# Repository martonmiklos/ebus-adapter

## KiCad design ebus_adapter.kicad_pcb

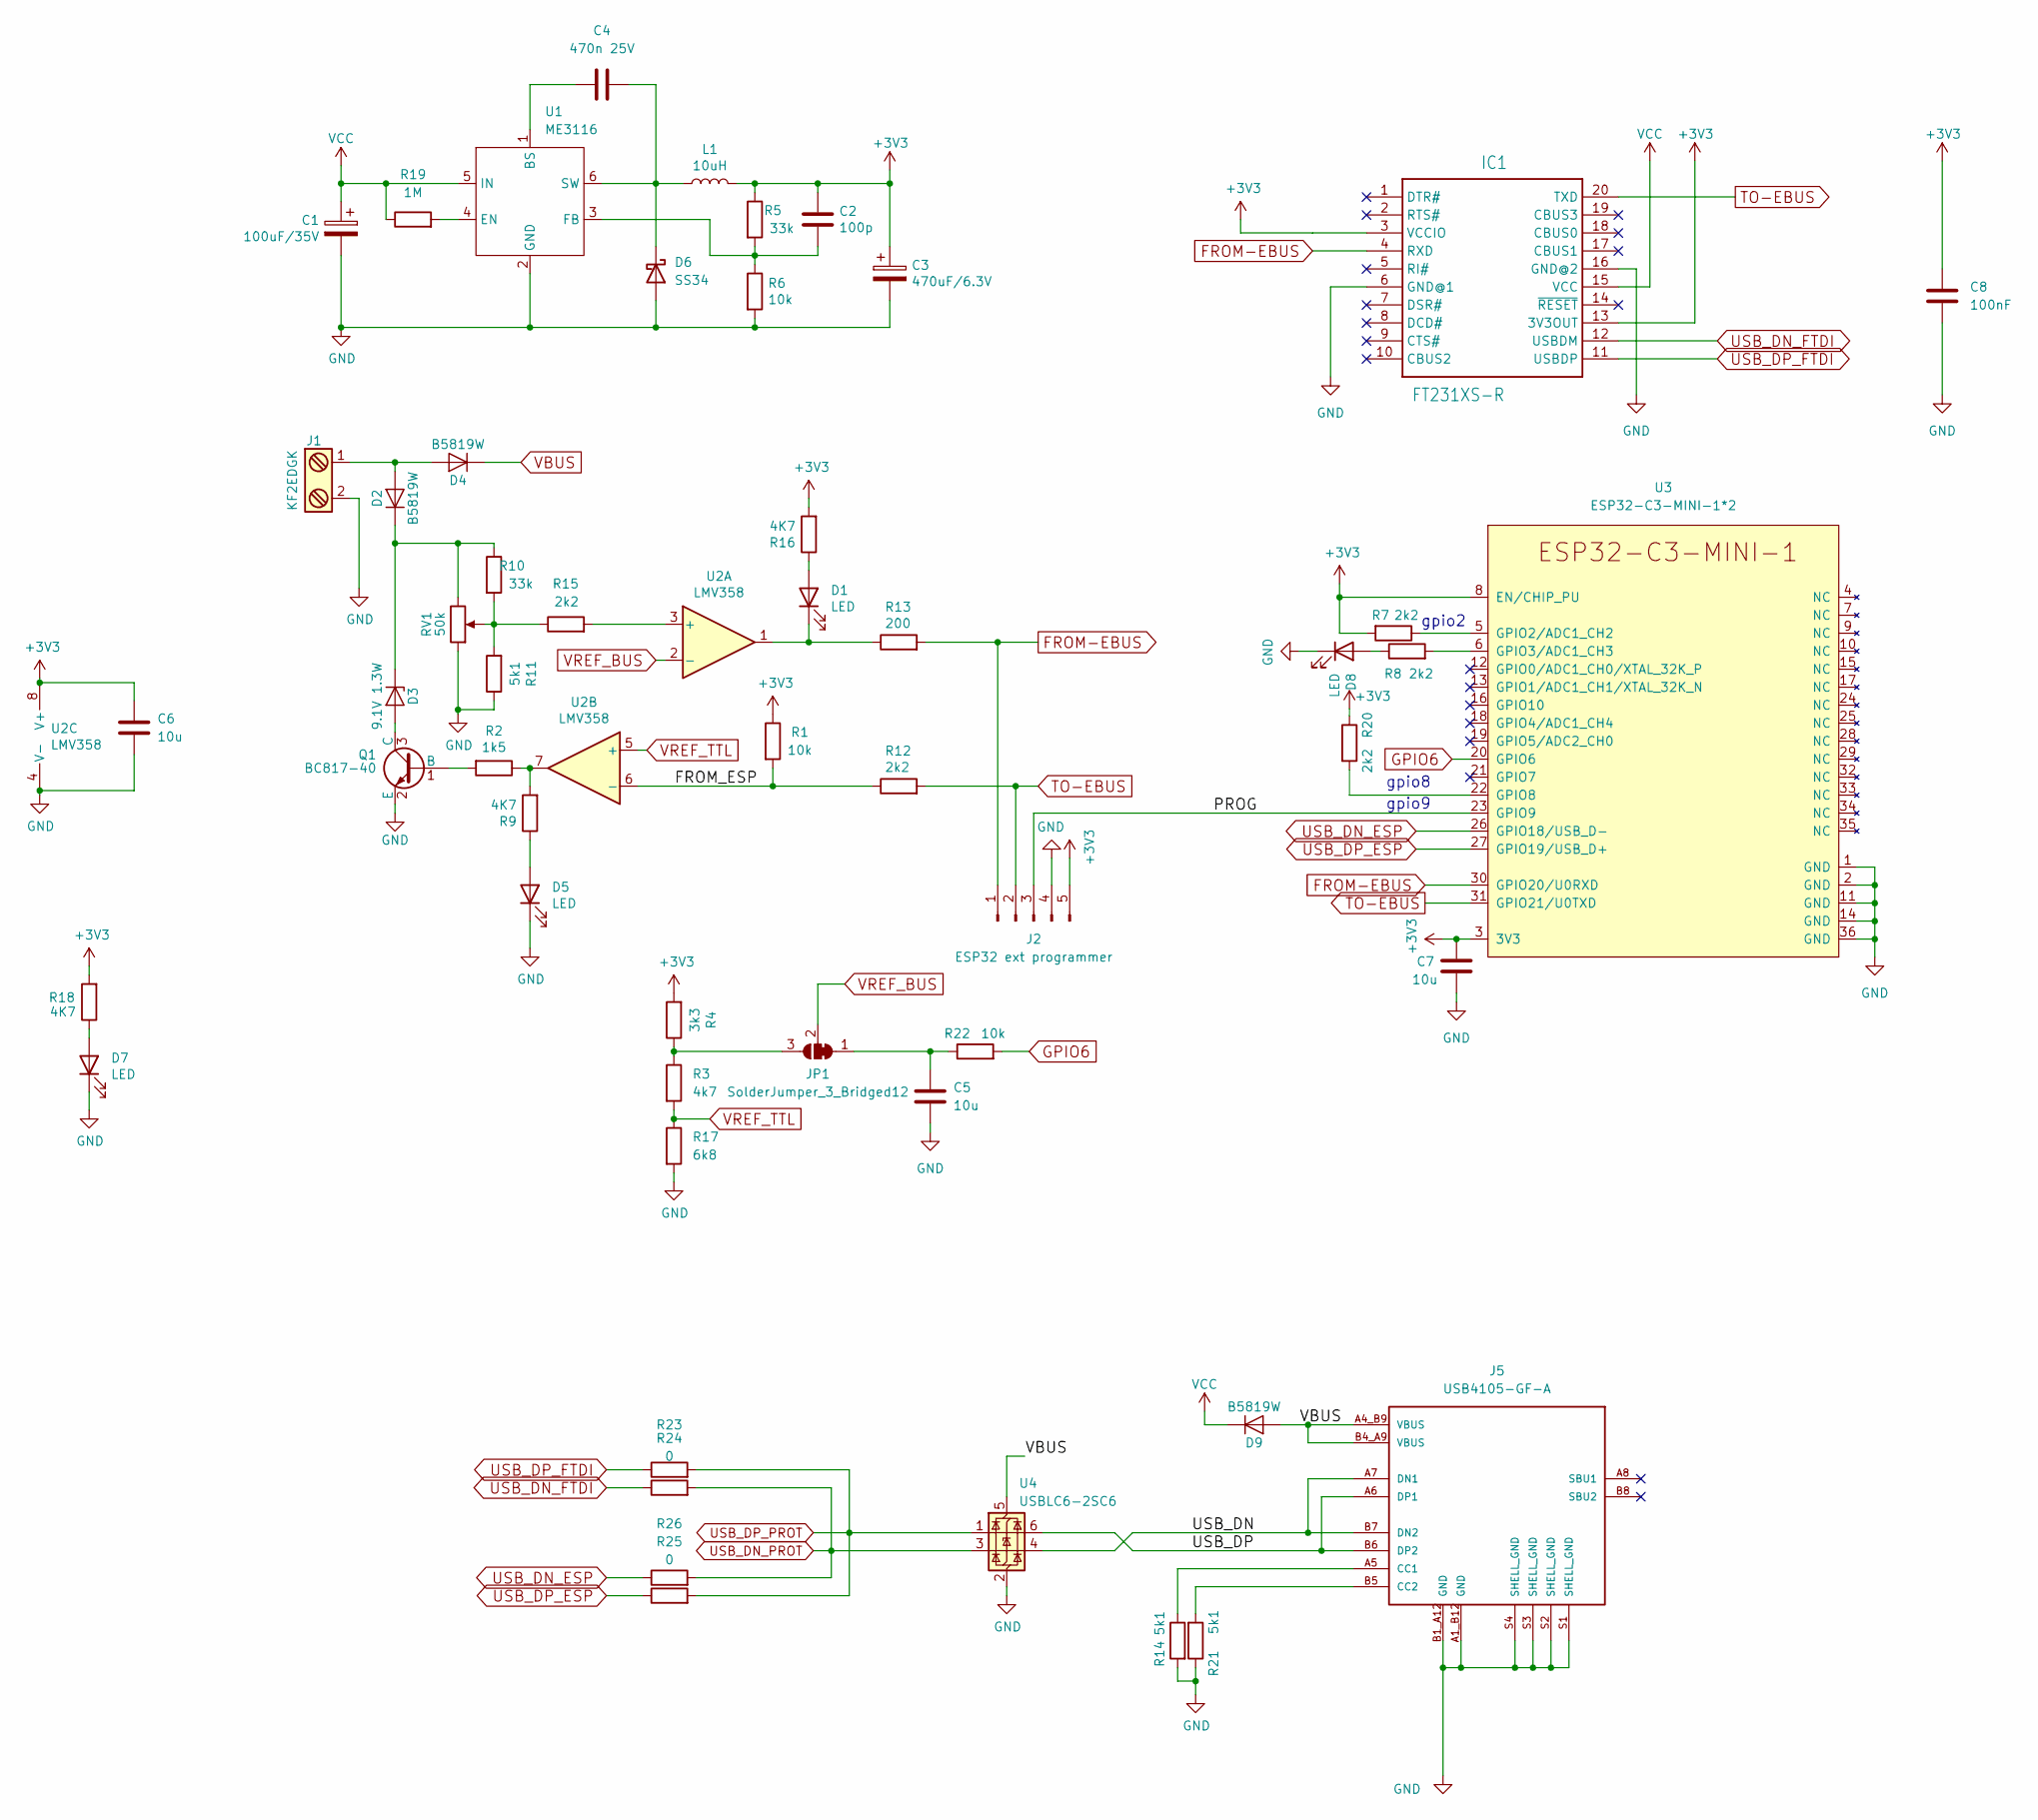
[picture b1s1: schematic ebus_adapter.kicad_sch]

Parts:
C1: 100uF/35V; CP_Elec_6.3x7.7; LCSC C240562
C2: 100p; C_0603_1608Metric; LCSC C14858
C3: 470uF/6.3V; CP_Elec_6.3x7.7; LCSC C3354
C4: 470n 25V; C_0603_1608Metric; LCSC C1623
C5, C6, C7: 10u; C_0603_1608Metric; LCSC C19702
C8: 100nF; C_0603_1608Metric; LCSC C19702
D1, D5, D7, D8: LED; LED_0603_1608Metric; LCSC C2286
D2, D4, D9: B5819W; D_SOD-123; LCSC C8598
D3: 9.1V 1.3W; D_MELF; LCSC C173488
D6: SS34; D_MELF; LCSC C8678
IC1: FT231XS-R; SOP63P599X175-20N
J1: KF2EDGK; CONN-TH_P5.08_HT508R-5.08-2P; LCSC C577832
J2: ESP32 ext programmer; PinHeader_1x05_P1.27mm_Vertical
J5: USB4105-GF-A; GCT_USB4105-GF-A_1; PARTREV A3
JP1: SolderJumper_3_Bridged12; SolderJumper-3_P1.3mm_Bridged12_RoundedPad1.0x1.5mm
L1: 10uH; L_Bourns-SRN6028; LCSC C9164
Q1: BC817-40; SOT-23; LCSC C2150
R1, R6, R22: 10k; R_0603_1608Metric; LCSC C25804
R2: 1k5; R_0603_1608Metric; LCSC C22843
R3: 4k7; R_0603_1608Metric; LCSC C23162
R4: 3k3; R_0603_1608Metric; LCSC C22978
R5, R10: 33k; R_0603_1608Metric; LCSC C4216
R7, R8, R12, R15, R20: 2k2; R_0603_1608Metric; LCSC C4190
R9, R16, R18: 4K7; R_0603_1608Metric; LCSC C4190
R11, R14, R21: 5k1; R_0603_1608Metric; LCSC C23186
R13: 200; R_0603_1608Metric; LCSC C8218
R17: 6k8; R_0603_1608Metric; LCSC C23212
R19: 1M; R_0603_1608Metric; LCSC C22935
R23, R24, R25, R26: 0; R_0603_1608Metric
RV1: 50k; Potentiometer_Bourns_3296W_Vertical; LCSC_IGNORE C118911
U1: ME3116; SOT-23-6; LCSC C97643
U2: LMV358; SOIC-8_3.9x4.9mm_P1.27mm; LCSC C63813
U3: ESP32-C3-MINI-1*2; ESP32-C3-MINI-1; LCSC C2934569
U4: USBLC6-2SC6; SOT-23-6

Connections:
+3V3: C2.1, C3.1, C6.1, C7.1, C8.1, IC1.3 (VCCIO), IC1.13 (3V3OUT), J2.5, L1.2, R1.1, R4.2, R5.1, R7.2, R16.2, R18.2, R20.1, U2.8 (V+), U3.3 (3V3), U3.8 (EN/CHIP_PU)
/FROM_ESP: R1.2, R12.1, U2.6 (-)
/PROG: J2.3, U3.23 (GPIO9)
/USB_DN: J5.A7 (DN1), J5.B7 (DN2), U4.4 (I/O2)
/USB_DP: J5.A6 (DP1), J5.B6 (DP2), U4.6 (I/O1)
FROM-EBUS: IC1.4 (RXD), J2.1, R13.2, U3.30 (GPIO20/U0RXD)
GND: C1.2, C3.2, C5.2, C6.2, C7.2, C8.2, D5.1 (K), D6.2 (A), D7.1 (K), D8.1 (K), IC1.6 (GND@1), IC1.16 (GND@2), J1.2, J2.4, J5.A1_B12 (GND), J5.B1_A12 (GND), J5.S1 (SHELL_GND), J5.S2 (SHELL_GND), J5.S3 (SHELL_GND), J5.S4 (SHELL_GND), Q1.2 (E), R6.2, R11.1, R14.2, R17.2, R21.1, RV1.1, U1.2 (GND), U2.4 (V-), U3.1 (GND), U3.2 (GND), U3.11 (GND), U3.14 (GND), U3.36 (GND), U4.2 (GND)
GPIO6: R22.2, U3.20 (GPIO6)
unnamed: D1.2 (A), R16.1
unnamed: D1.1 (K), R13.1, U2.1
unnamed: D2.2 (A), D4.2 (A), J1.1
unnamed: D2.1 (K), D3.1 (K), R10.1, RV1.3
unnamed: D3.2 (A), Q1.3 (C)
unnamed: D5.2 (A), R9.1
unnamed: C4.2, D6.1 (K), L1.1, U1.6 (SW)
unnamed: D7.2 (A), R18.1
unnamed: D8.2 (A), R8.1
unnamed: J5.A5 (CC1), R14.1
unnamed: J5.B5 (CC2), R21.2
unnamed: C5.1, JP1.1 (A), R22.1
unnamed: JP1.3 (B), R3.1, R4.1
unnamed: Q1.1 (B), R2.2
unnamed: R2.1, R9.2, U2.7
unnamed: R10.2, R11.2, R15.1, RV1.2
unnamed: C4.1, U1.1 (BS)
unnamed: R19.2, U1.4 (EN)
unnamed: C2.2, R5.2, R6.1, U1.3 (FB)
unnamed: R15.2, U2.3 (+)
unnamed: R7.1, U3.5 (GPIO2/ADC1_CH2)
unnamed: R8.2, U3.6 (GPIO3/ADC1_CH3)
unnamed: R20.2, U3.22 (GPIO8)
TO-EBUS: IC1.20 (TXD), J2.2, R12.2, U3.31 (GPIO21/U0TXD)
USB_DN_ESP: R26.1, U3.26 (GPIO18/USB_D-)
USB_DN_FTDI: IC1.12 (USBDM), R24.1
USB_DN_PROT: R24.2, R26.2, U4.3 (I/O2)
USB_DP_ESP: R25.1, U3.27 (GPIO19/USB_D+)
USB_DP_FTDI: IC1.11 (USBDP), R23.1
USB_DP_PROT: R23.2, R25.2, U4.1 (I/O1)
VBUS: D4.1 (K), D9.2 (A), J5.A4_B9 (VBUS), J5.B4_A9 (VBUS), U4.5 (VBUS)
VCC: C1.1, D9.1 (K), IC1.15 (VCC), R19.1, U1.5 (IN)
VREF_BUS: JP1.2 (C), U2.2 (-)
VREF_TTL: R3.2, R17.1, U2.5 (+)

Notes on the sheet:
gpio2
gpio8
gpio9

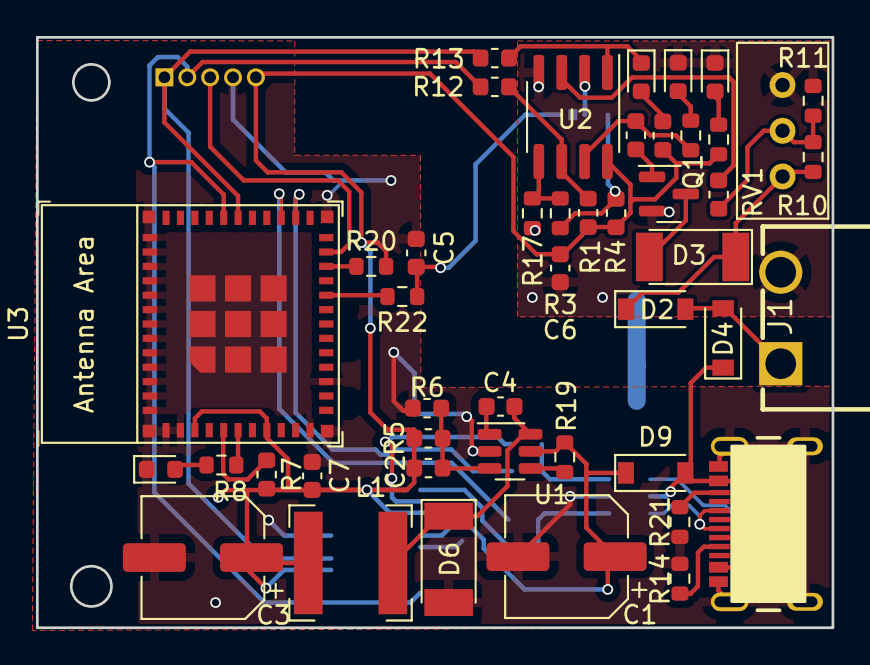
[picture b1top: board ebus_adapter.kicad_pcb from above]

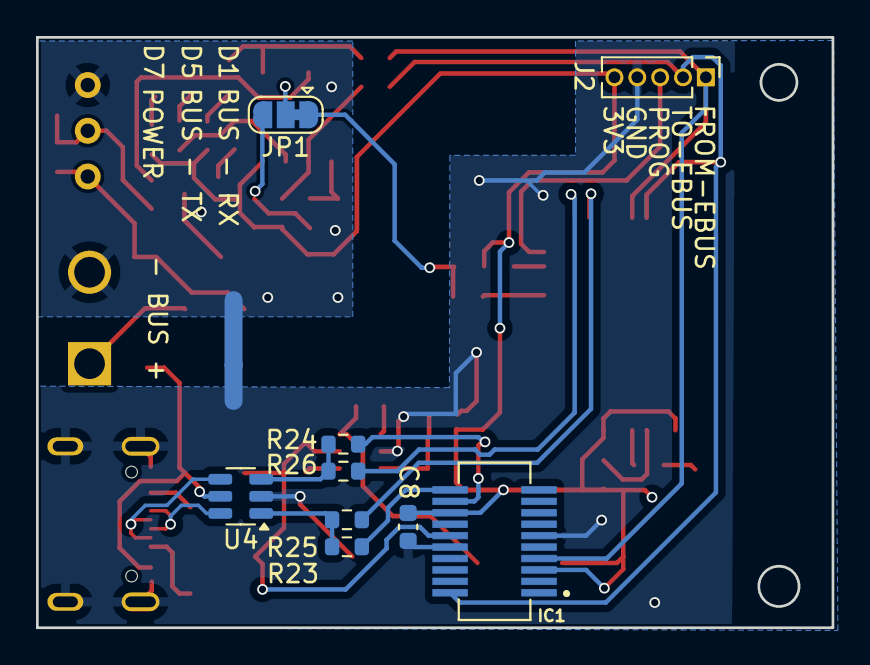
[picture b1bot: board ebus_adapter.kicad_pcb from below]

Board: 2 copper layers, 44.2 x 32.8 mm, 55 parts (9 on the bottom side), 42 nets.

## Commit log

2026-04-10 Daily save
